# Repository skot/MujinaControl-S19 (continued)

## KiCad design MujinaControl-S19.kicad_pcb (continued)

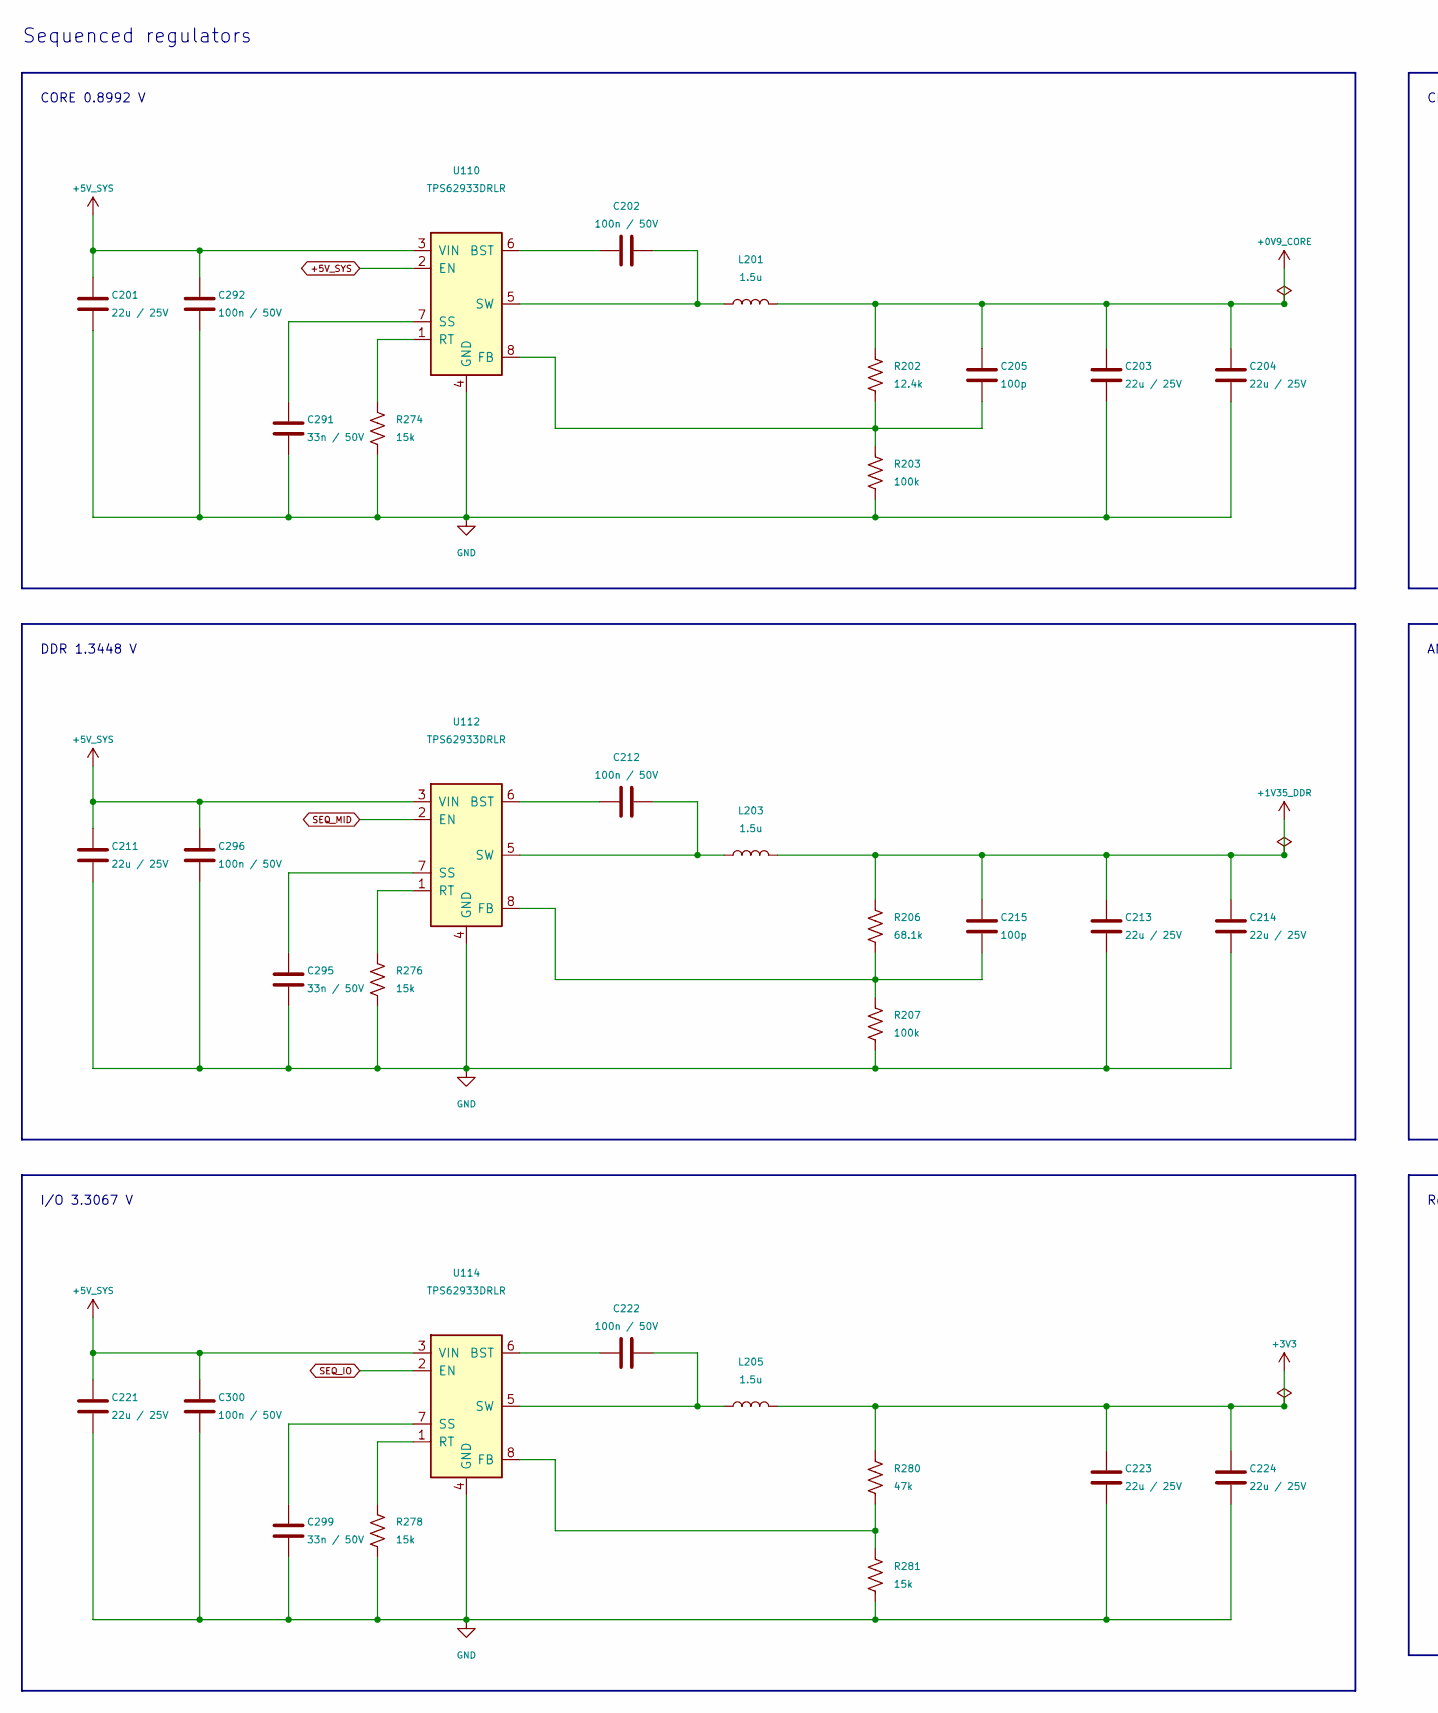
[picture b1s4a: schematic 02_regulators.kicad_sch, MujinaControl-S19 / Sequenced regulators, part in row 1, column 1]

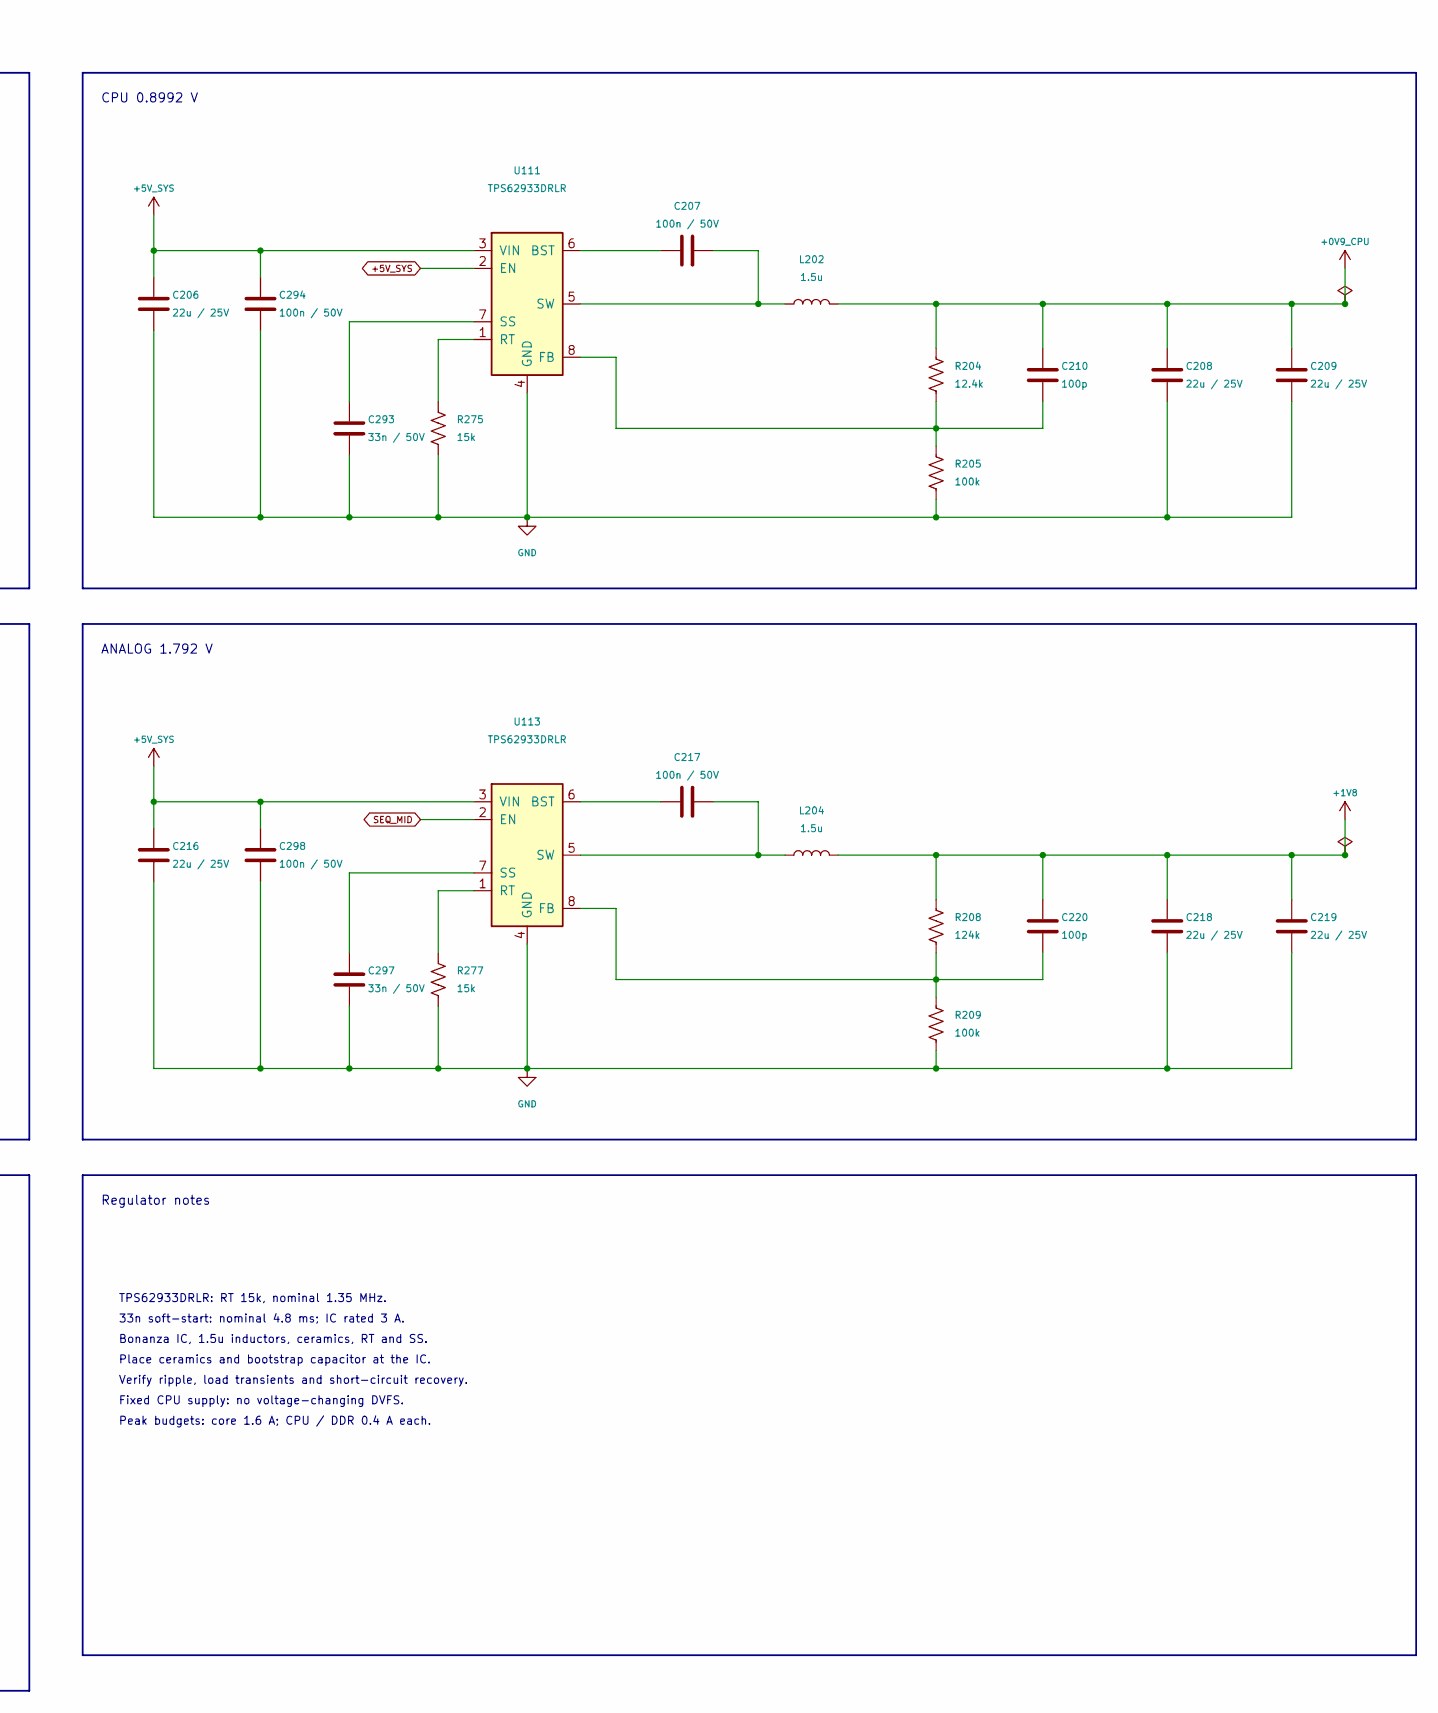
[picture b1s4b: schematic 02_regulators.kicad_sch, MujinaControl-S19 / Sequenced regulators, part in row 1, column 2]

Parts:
C201, C203, C204, C206, C208, C209, C211, C213, C214, C216, C218, C219, C221, C223, C224: 22u / 25V; C_0805_2012Metric; MPN CL21A226MAQNNNE; LCSC C45783
C202, C207, C212, C217, C222, C292, C294, C296, C298, C300: 100n / 50V; C_0402_1005Metric; MPN CL05B104KB54PNC; LCSC C307331
C205, C210, C215, C220: 100p; C_0402_1005Metric; MPN 0402CG101J500NT; LCSC C1546
C291, C293, C295, C297, C299: 33n / 50V; C_0603_1608Metric; MPN CL10B333KB8NNNC; LCSC C21117
L201, L202, L203, L204, L205: 1.5u; IND-SMD_L2.0-W1.6; MPN FTC201612S1R5MBCA; LCSC C5832350
R202, R204: 12.4k; R_0402_1005Metric; MPN RC0402FR-0712K4L; LCSC C138060
R203, R205, R207, R209: 100k; R_0402_1005Metric; MPN 0402WGF1003TCE; LCSC C25741
R206: 68.1k; R_0402_1005Metric; MPN RC0402FR-0768K1L; LCSC C276276
R208: 124k; R_0402_1005Metric; MPN 0402WGF1243TCE; LCSC C36777
R274, R275, R276, R277, R278, R281: 15k; R_0402_1005Metric; MPN 0402WGF1502TCE; LCSC C25756
R280: 47k; R_0402_1005Metric; MPN 0402WGF4702TCE; LCSC C25792
U110, U111, U112, U113, U114: TPS62933DRLR; SOT-583-8_L2.1-W1.2-P0.50-LS1.6-BR; MPN TPS62933DRLR; LCSC C3200405

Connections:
+0V9_CORE: C203.1, C204.1, C205.1, L201.2, R202.1; also elsewhere on the board
+0V9_CPU: C208.1, C209.1, C210.1, L202.2, R204.1; also elsewhere on the board
+1V8: C218.1, C219.1, C220.1, L204.2, R208.1; also elsewhere on the board
+1V35_DDR: C213.1, C214.1, C215.1, L203.2, R206.1; also elsewhere on the board
+3V3: C223.1, C224.1, L205.2, R280.1; also elsewhere on the board
+5V_SYS: C201.1, C206.1, C211.1, C216.1, C221.1, C292.1, C294.1, C296.1, C298.1, C300.1, U110.2 (EN), U110.3 (VIN), U111.2 (EN), U111.3 (VIN), U112.3 (VIN), U113.3 (VIN), U114.3 (VIN); also elsewhere on the board
GND: C201.2, C203.2, C204.2, C206.2, C208.2, C209.2, C211.2, C213.2, C214.2, C216.2, C218.2, C219.2, C221.2, C223.2, C224.2, C291.2, C292.2, C293.2, C294.2, C295.2, C296.2, C297.2, C298.2, C299.2, C300.2, R203.2, R205.2, R207.2, R209.2, R274.2, R275.2, R276.2, R277.2, R278.2, R281.2, U110.4 (GND), U111.4 (GND), U112.4 (GND), U113.4 (GND), U114.4 (GND); also elsewhere on the board
unnamed: C202.1, U110.6 (BST)
unnamed: C205.2, R202.2, R203.1, U110.8 (FB)
unnamed: R274.1, U110.1 (RT)
unnamed: C291.1, U110.7 (SS)
unnamed: C202.2, L201.1, U110.5 (SW)
unnamed: C207.1, U111.6 (BST)
unnamed: C210.2, R204.2, R205.1, U111.8 (FB)
unnamed: R275.1, U111.1 (RT)
unnamed: C293.1, U111.7 (SS)
unnamed: C207.2, L202.1, U111.5 (SW)
unnamed: C212.1, U112.6 (BST)
unnamed: C215.2, R206.2, R207.1, U112.8 (FB)
unnamed: R276.1, U112.1 (RT)
unnamed: C295.1, U112.7 (SS)
unnamed: C212.2, L203.1, U112.5 (SW)
unnamed: C217.1, U113.6 (BST)
unnamed: C220.2, R208.2, R209.1, U113.8 (FB)
unnamed: R277.1, U113.1 (RT)
unnamed: C297.1, U113.7 (SS)
unnamed: C217.2, L204.1, U113.5 (SW)
unnamed: C222.1, U114.6 (BST)
unnamed: R280.2, R281.1, U114.8 (FB)
unnamed: R278.1, U114.1 (RT)
unnamed: C299.1, U114.7 (SS)
unnamed: C222.2, L205.1, U114.5 (SW)
SEQ_IO: U114.2 (EN); also elsewhere on the board
SEQ_MID: U112.2 (EN), U113.2 (EN); also elsewhere on the board

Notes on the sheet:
CPU 0.8992 V
DDR 1.3448 V
Peak budgets: core 1.6 A; CPU / DDR 0.4 A each.
CORE 0.8992 V
Verify ripple, load transients and short-circuit recovery.
ANALOG 1.792 V
Place ceramics and bootstrap capacitor at the IC.
Bonanza IC, 1.5u inductors, ceramics, RT and SS.
Sequenced regulators
I/O 3.3067 V
Fixed CPU supply: no voltage-changing DVFS.
TPS62933DRLR: RT 15k, nominal 1.35 MHz.
Regulator notes
33n soft-start: nominal 4.8 ms; IC rated 3 A.

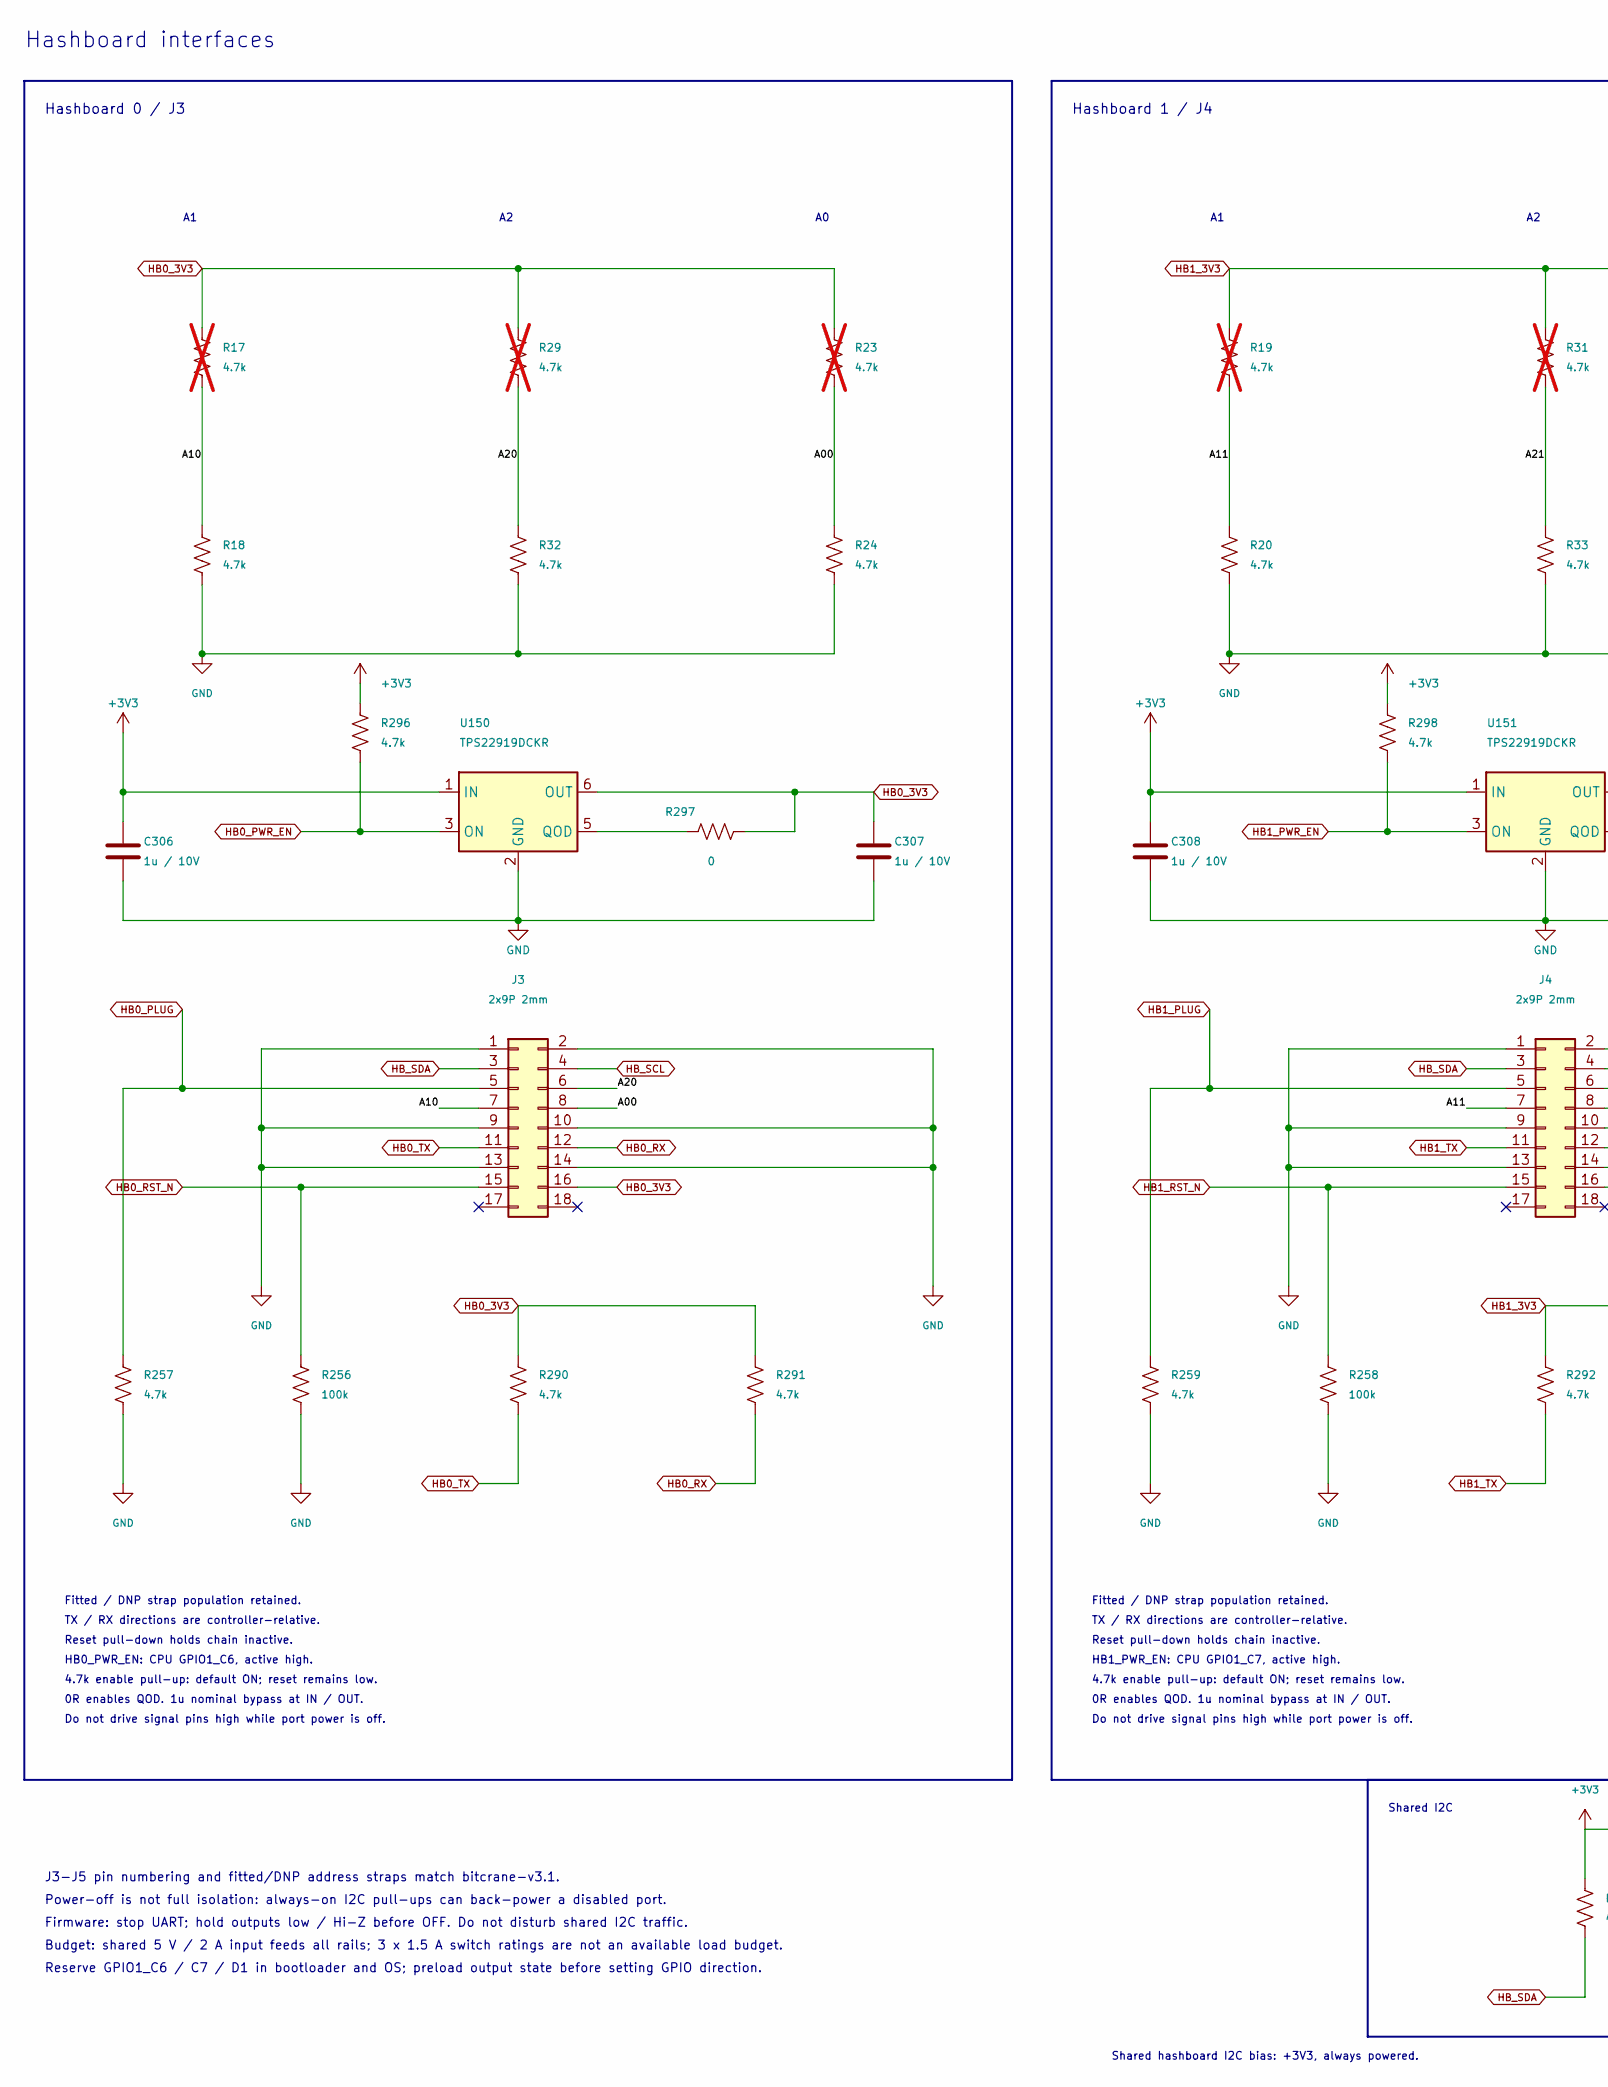
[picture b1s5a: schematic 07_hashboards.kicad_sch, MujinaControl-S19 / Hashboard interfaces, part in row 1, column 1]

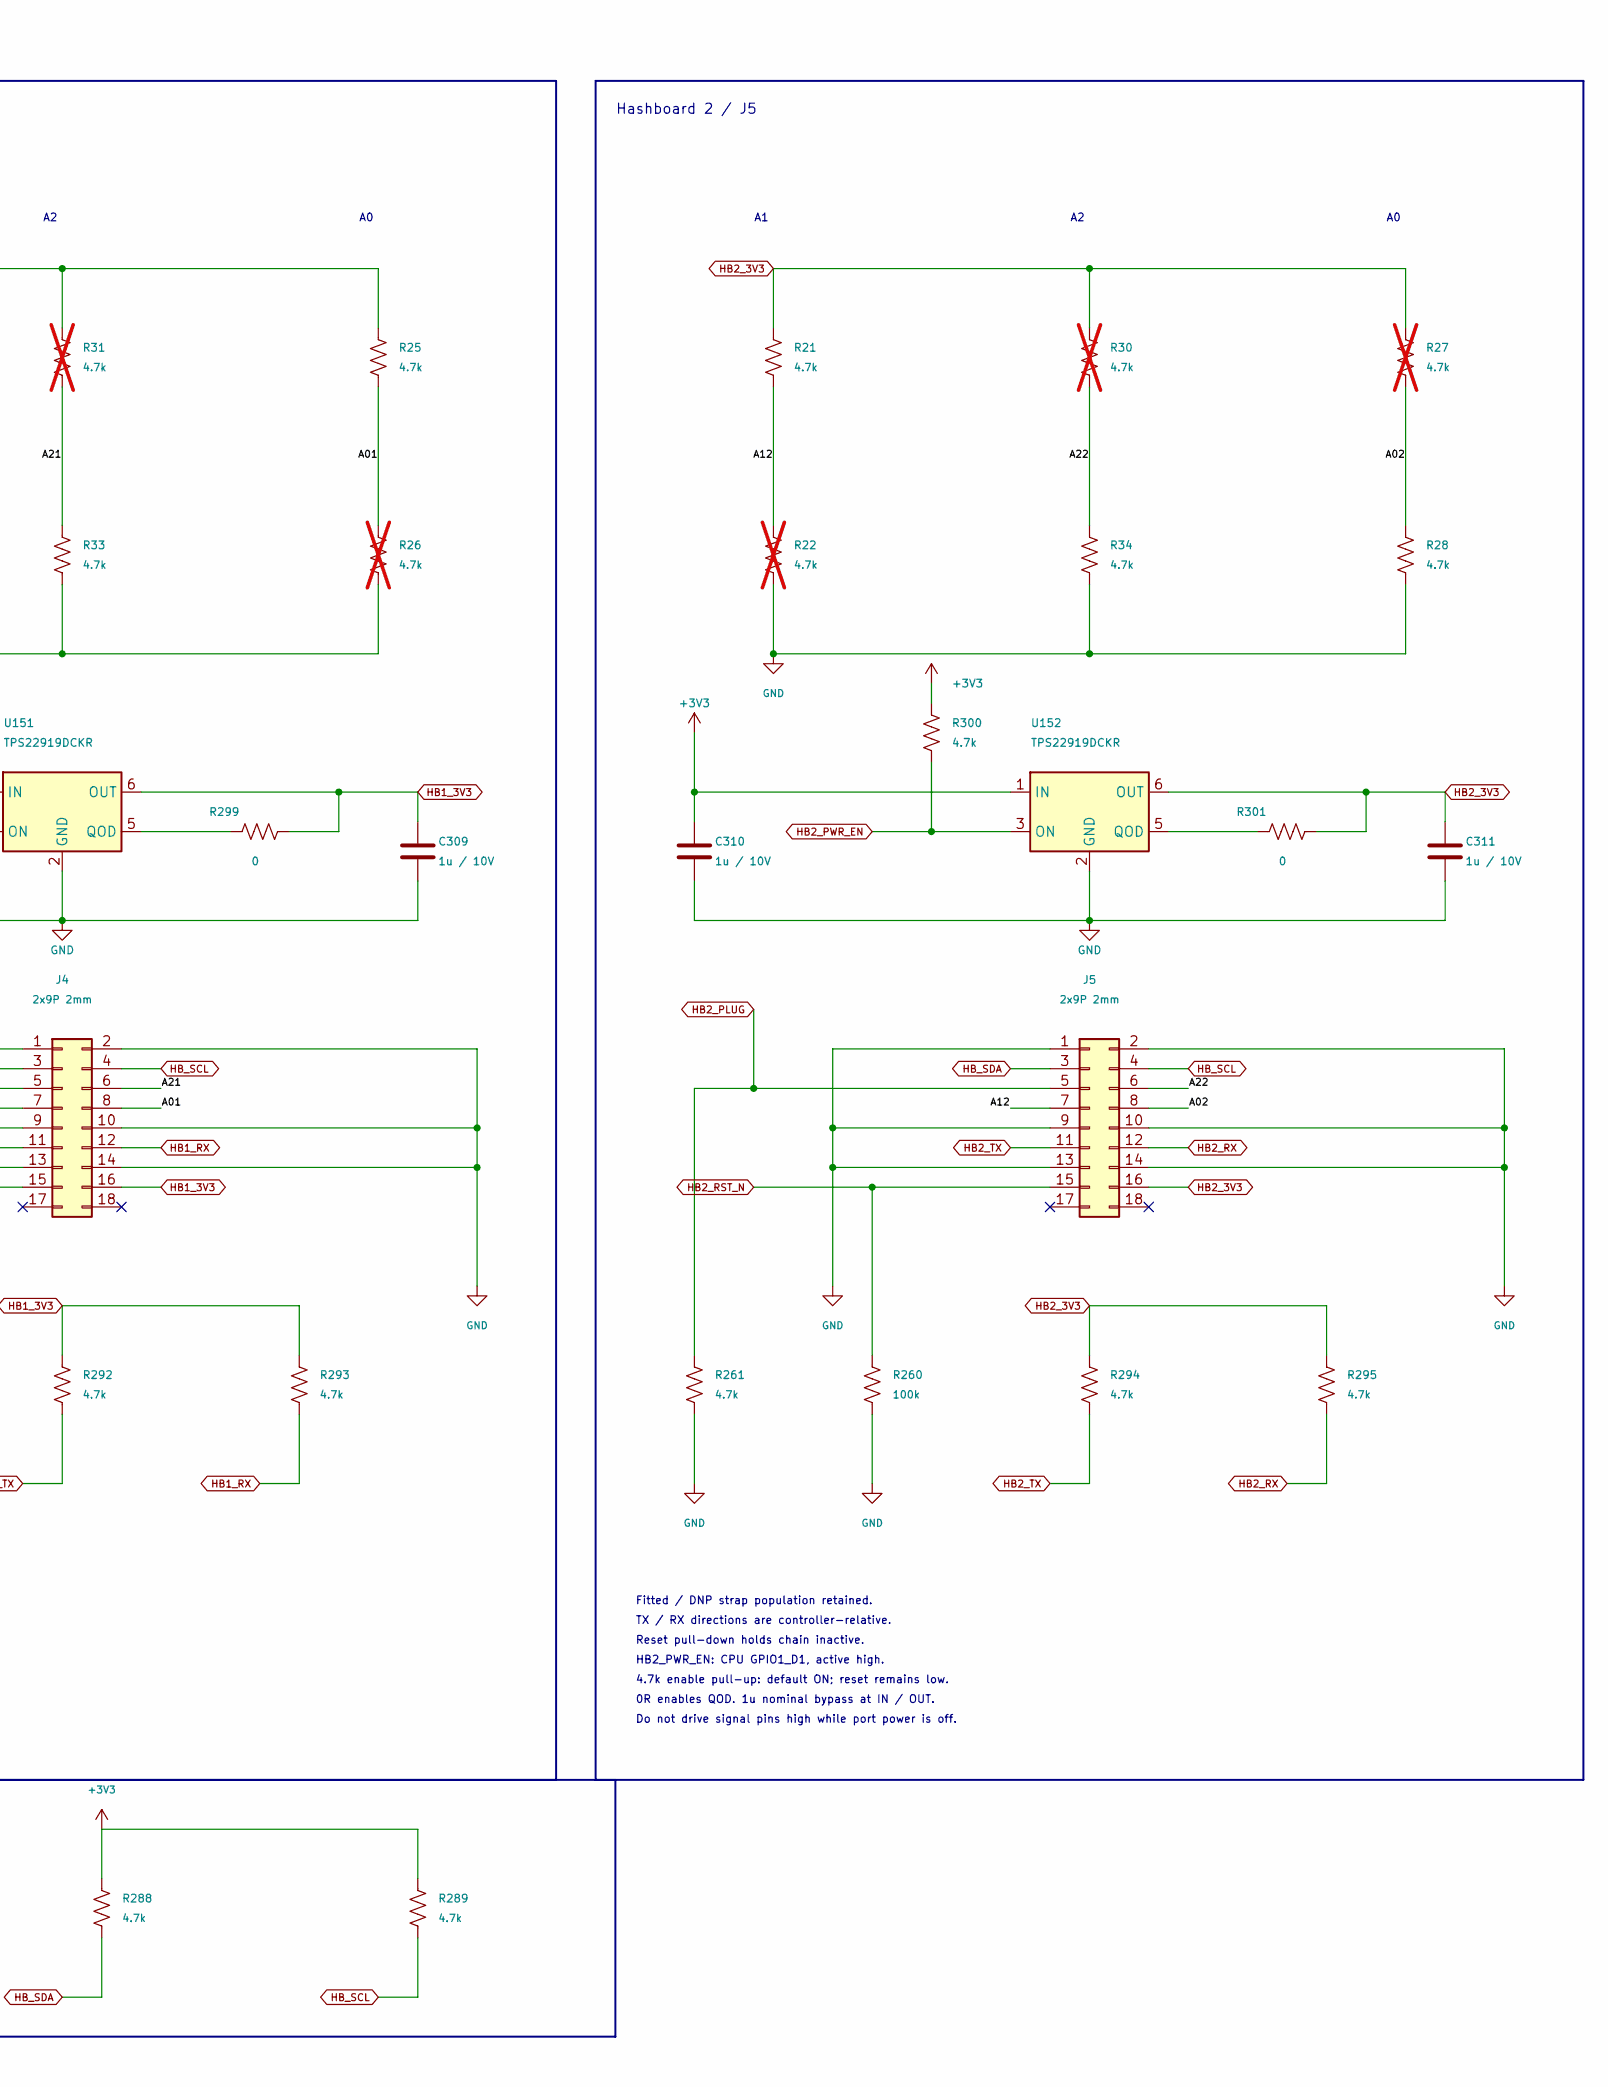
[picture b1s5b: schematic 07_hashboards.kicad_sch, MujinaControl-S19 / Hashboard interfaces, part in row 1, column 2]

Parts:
C306, C307, C308, C309, C310, C311: 1u / 10V; C_0402_1005Metric; MPN CL05A105KA5NQNC; LCSC C52923
J3, J4, J5: 2x9P 2mm; CONN-TH_X2026WV-2-09D-46SN; MPN X2026WV-2x09D-46SN; LCSC C437089
R17, R19, R22, R23, R26, R27, R29, R30, R31: 4.7k; R_0402_1005Metric; MPN 0402WGF4701TCE; LCSC C25900; not fitted
R18, R20, R21, R24, R25, R28, R32, R33, R34, R257, R259, R261, R288, R289, R290, R291, R292, R293, R294, R295, R296, R298, R300: 4.7k; R_0402_1005Metric; MPN 0402WGF4701TCE; LCSC C25900
R256, R258, R260: 100k; R_0402_1005Metric; MPN 0402WGF1003TCE; LCSC C25741
R297, R299, R301: 0; R_0402_1005Metric; MPN 0402WGF0000TCE; LCSC C17168
U150, U151, U152: TPS22919DCKR; SOT-363_SC-70-6; MPN TPS22919DCKR; LCSC C2149796

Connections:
+3V3: C306.1, C308.1, C310.1, R288.1, R289.1, R296.1, R298.1, R300.1, U150.1 (IN), U151.1 (IN), U152.1 (IN); also elsewhere on the board
/Three hashboard interfaces/A00: J3.8, R23.2, R24.1
/Three hashboard interfaces/A01: J4.8, R25.2, R26.1
/Three hashboard interfaces/A02: J5.8, R27.2, R28.1
/Three hashboard interfaces/A10: J3.7, R17.2, R18.1
/Three hashboard interfaces/A11: J4.7, R19.2, R20.1
/Three hashboard interfaces/A12: J5.7, R21.2, R22.1
/Three hashboard interfaces/A20: J3.6, R29.2, R32.1
/Three hashboard interfaces/A21: J4.6, R31.2, R33.1
/Three hashboard interfaces/A22: J5.6, R30.2, R34.1
GND: C306.2, C307.2, C308.2, C309.2, C310.2, C311.2, J3.1, J3.2, J3.9, J3.10, J3.13, J3.14, J4.1, J4.2, J4.9, J4.10, J4.13, J4.14, J5.1, J5.2, J5.9, J5.10, J5.13, J5.14, R18.2, R20.2, R22.2, R24.2, R26.2, R28.2, R32.2, R33.2, R34.2, R256.2, R257.2, R258.2, R259.2, R260.2, R261.2, U150.2 (GND), U151.2 (GND), U152.2 (GND); also elsewhere on the board
HB0_3V3: C307.1, J3.16, R17.1, R23.1, R29.1, R290.1, R291.1, R297.2, U150.6 (OUT)
HB0_PLUG: J3.5, R257.1; also elsewhere on the board
HB0_PWR_EN: R296.2, U150.3 (ON); also elsewhere on the board
HB0_RST_N: J3.15, R256.1; also elsewhere on the board
HB0_RX: J3.12, R291.2; also elsewhere on the board
HB0_TX: J3.11, R290.2; also elsewhere on the board
HB1_3V3: C309.1, J4.16, R19.1, R25.1, R31.1, R292.1, R293.1, R299.2, U151.6 (OUT)
HB1_PLUG: J4.5, R259.1; also elsewhere on the board
HB1_PWR_EN: R298.2, U151.3 (ON); also elsewhere on the board
HB1_RST_N: J4.15, R258.1; also elsewhere on the board
HB1_RX: J4.12, R293.2; also elsewhere on the board
HB1_TX: J4.11, R292.2; also elsewhere on the board
HB2_3V3: C311.1, J5.16, R21.1, R27.1, R30.1, R294.1, R295.1, R301.2, U152.6 (OUT)
HB2_PLUG: J5.5, R261.1; also elsewhere on the board
HB2_PWR_EN: R300.2, U152.3 (ON); also elsewhere on the board
HB2_RST_N: J5.15, R260.1; also elsewhere on the board
HB2_RX: J5.12, R295.2; also elsewhere on the board
HB2_TX: J5.11, R294.2; also elsewhere on the board
HB_SCL: J3.4, J4.4, J5.4, R289.2; also elsewhere on the board
HB_SDA: J3.3, J4.3, J5.3, R288.2; also elsewhere on the board
unnamed: R297.1, U150.5 (QOD)
unnamed: R299.1, U151.5 (QOD)
unnamed: R301.1, U152.5 (QOD)

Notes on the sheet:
Fitted / DNP strap population retained.
Hashboard 1 / J4
Reset pull-down holds chain inactive.
HB0_PWR_EN: CPU GPIO1_C6, active high.
Power-off is not full isolation: always-on I2C pull-ups can back-power a disabled port.
TX / RX directions are controller-relative.
Do not drive signal pins high while port power is off.
HB1_PWR_EN: CPU GPIO1_C7, active high.
J3-J5 pin numbering and fitted/DNP address straps match bitcrane-v3.1.
4.7k enable pull-up: default ON; reset remains low.
0R enables QOD. 1u nominal bypass at IN / OUT.
Hashboard 0 / J3
Shared I2C
Hashboard 2 / J5
Hashboard interfaces
HB2_PWR_EN: CPU GPIO1_D1, active high.
Budget: shared 5 V / 2 A input feeds all rails; 3 x 1.5 A switch ratings are not an available load budget.
Reserve GPIO1_C6 / C7 / D1 in bootloader and OS; preload output state before setting GPIO direction.
Firmware: stop UART; hold outputs low / Hi-Z before OFF. Do not disturb shared I2C traffic.
Shared hashboard I2C bias: +3V3, always powered.

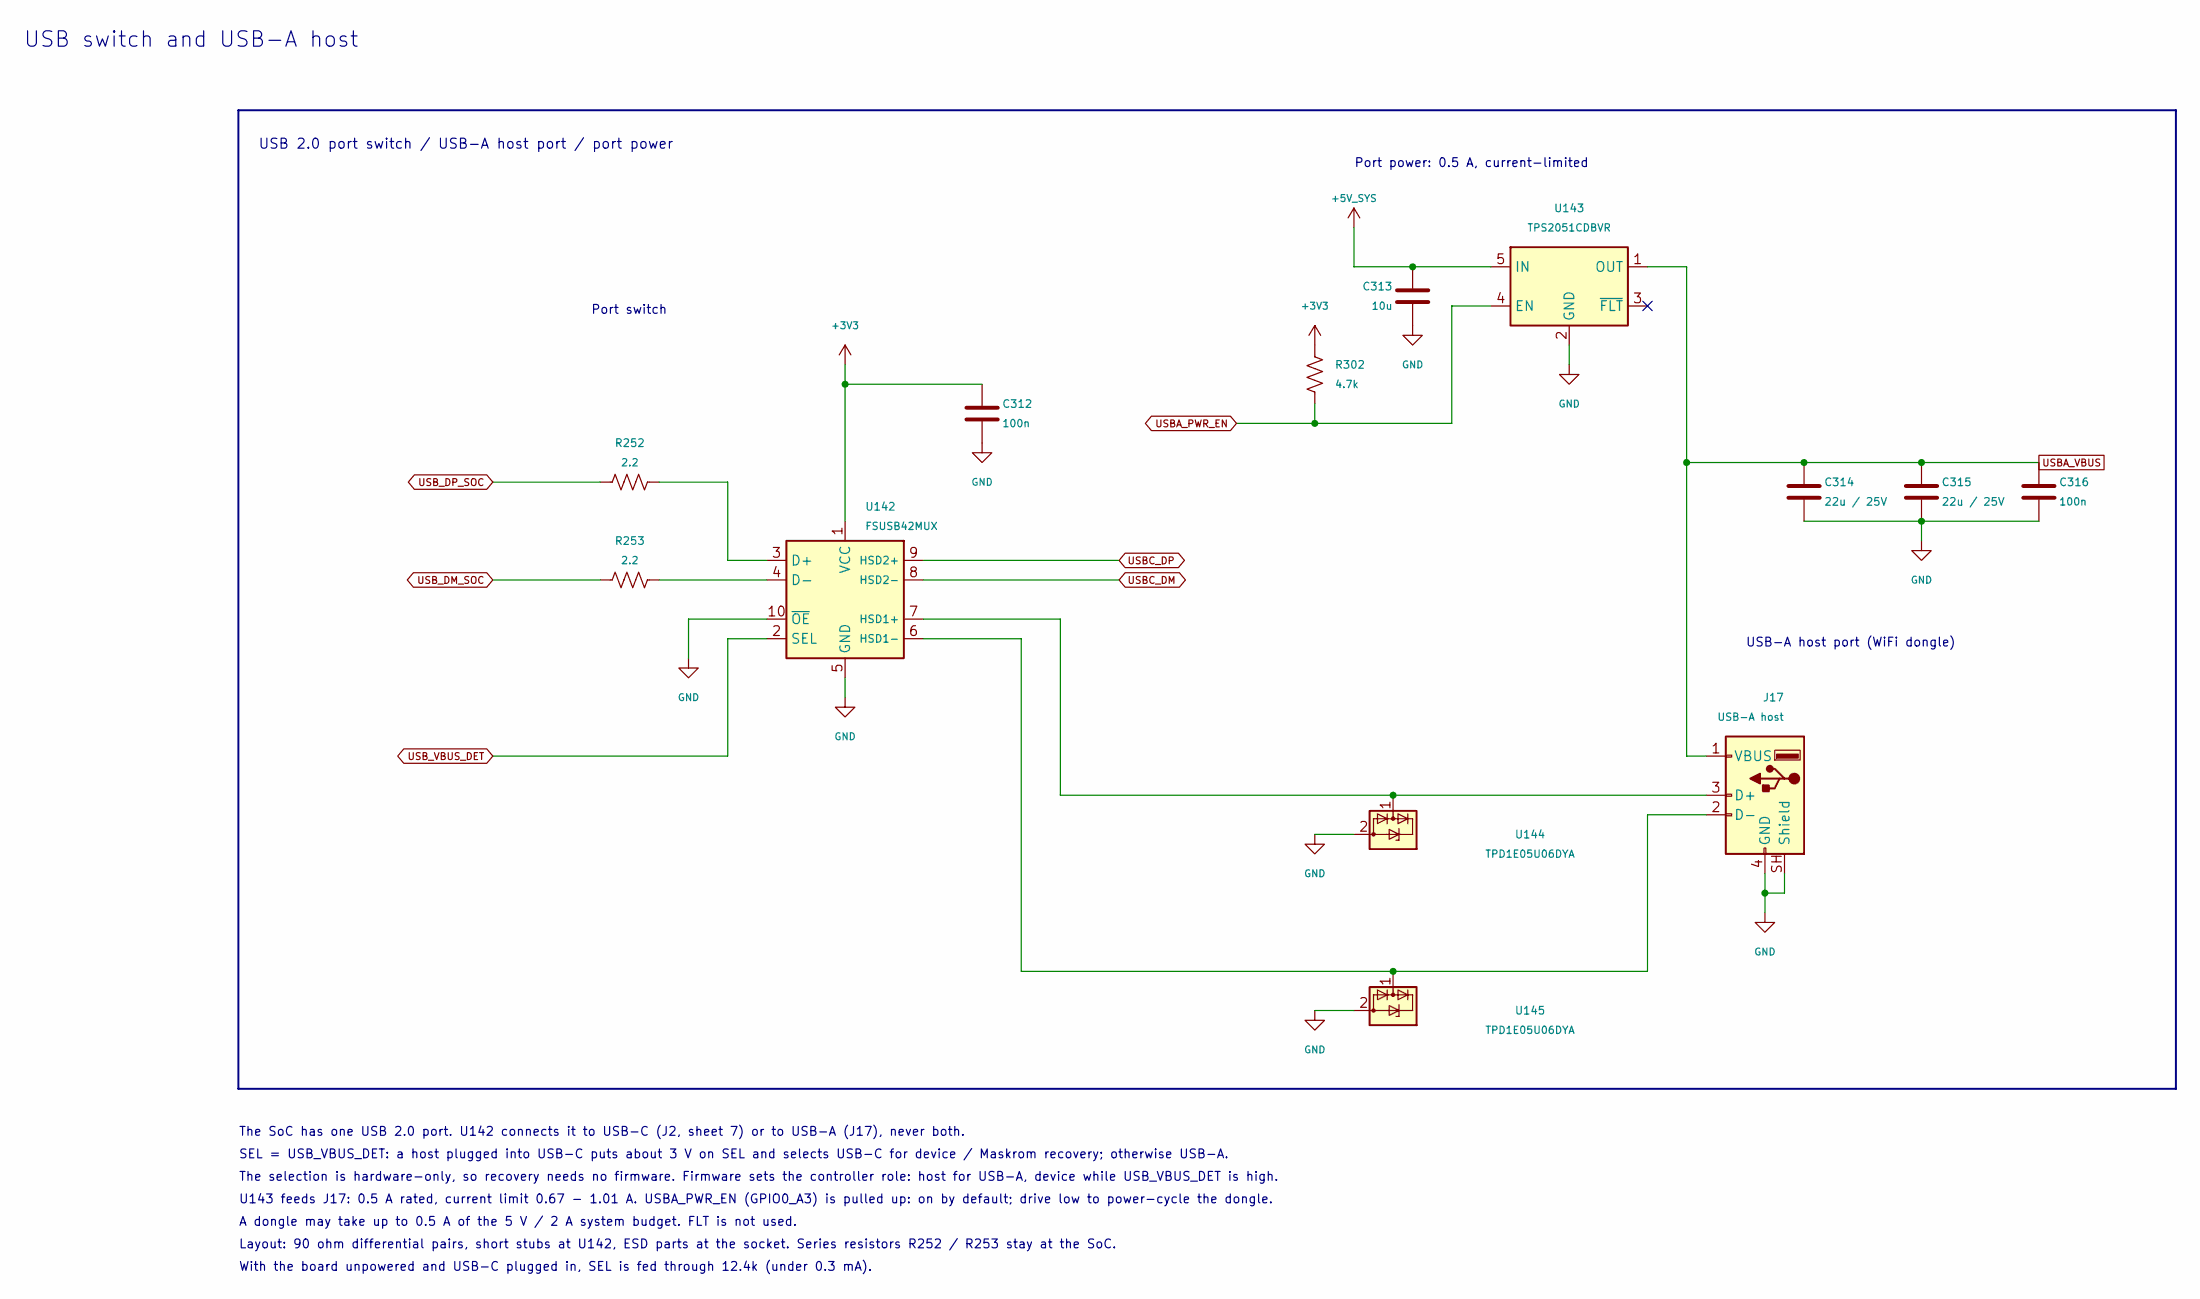
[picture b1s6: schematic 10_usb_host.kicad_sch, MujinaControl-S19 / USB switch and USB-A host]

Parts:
C312, C316: 100n; C_0402_1005Metric; MPN CL05B104KO5NNNC; LCSC C1525
C313: 10u; C_0805_2012Metric; MPN CL21A106KAYNNNE; LCSC C15850
C314, C315: 22u / 25V; C_0805_2012Metric; MPN CL21A226MAQNNNE; LCSC C45783
J17: USB-A host; USB_A_Molex_67643_Horizontal; MPN AF 90 WJDG; LCSC C456018
R252, R253: 2.2; R_0402_1005Metric; MPN RC0402FR-072R2L; LCSC C327251
R302: 4.7k; R_0402_1005Metric; MPN 0402WGF4701TCE; LCSC C25900
U142: FSUSB42MUX; MSOP-10_3x3mm_P0.5mm; MPN FSUSB42MUX; LCSC C11355
U143: TPS2051CDBVR; SOT-23-5; MPN TPS2051CDBVR; LCSC C129581
U144, U145: TPD1E05U06DYA; D_SOD-523; MPN TPD1E05U06DYA; LCSC C3702980

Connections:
+3V3: C312.1, R302.1, U142.1 (VCC); also elsewhere on the board
+5V_SYS: C313.1, U143.5 (IN); also elsewhere on the board
GND: C312.2, C313.2, C314.2, C315.2, C316.2, J17.4 (GND), J17.SH (Shield), U142.5 (GND), U142.10 (~OE), U143.2 (GND), U144.2 (GND), U145.2 (GND); also elsewhere on the board
unnamed: J17.3 (D+), U142.7 (HSD1+), U144.1 (I/O)
unnamed: J17.2 (D-), U142.6 (HSD1-), U145.1 (I/O)
unnamed: R252.2, U142.3 (D+)
unnamed: R253.2, U142.4 (D-)
USBA_PWR_EN: R302.2, U143.4 (EN); also elsewhere on the board
USBA_VBUS: C314.1, C315.1, C316.1, J17.1 (VBUS), U143.1 (OUT)
USBC_DM: U142.8 (HSD2-); also elsewhere on the board
USBC_DP: U142.9 (HSD2+); also elsewhere on the board
USB_DM_SOC: R253.1; also elsewhere on the board
USB_DP_SOC: R252.1; also elsewhere on the board
USB_VBUS_DET: U142.2 (SEL); also elsewhere on the board

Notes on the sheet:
USB 2.0 port switch / USB-A host port / port power
With the board unpowered and USB-C plugged in, SEL is fed through 12.4k (under 0.3 mA).
SEL = USB_VBUS_DET: a host plugged into USB-C puts about 3 V on SEL and selects USB-C for device / Maskrom recovery; otherwise USB-A.
U143 feeds J17: 0.5 A rated, current limit 0.67 - 1.01 A. USBA_PWR_EN (GPIO0_A3) is pulled up: on by default; drive low to power-cycle the dongle.
USB-A host port (WiFi dongle)
Layout: 90 ohm differential pairs, short stubs at U142, ESD parts at the socket. Series resistors R252 / R253 stay at the SoC.
The selection is hardware-only, so recovery needs no firmware. Firmware sets the controller role: host for USB-A, device while USB_VBUS_DET is high.
Port switch
A dongle may take up to 0.5 A of the 5 V / 2 A system budget. FLT is not used.
USB switch and USB-A host
The SoC has one USB 2.0 port. U142 connects it to USB-C (J2, sheet 7) or to USB-A (J17), never both.
Port power: 0.5 A, current-limited
